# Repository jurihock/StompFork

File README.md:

# StompFork

This project is about an active audio signal splitter that utilizes the TL074 opamp to drive multiple parallel stompboxes.

## Key features

- Split one line-level input into three outputs
- Direct output (unity from input buffer)
- Stompbox output 1 (level pot + output buffer)
- Stompbox output 2 (level pot + output buffer)

## Power supply

- Recommended 18 V
- Should work at 12 V
- May work at 9 V
- Series schottky protection included

## Impedance

- Hi‑Z input (~1 MΩ AC)
- Lo‑Z output (~100 Ω AC)

## Caps

Depending on your preference, you can use polarized electrolytic caps in the signal path, or you can replace them with "audiophile" film caps. For this purpose, the KiCad project includes larger footprints for `C1` and `C5-C7`. 

If you decide to use the polarized electrolytic caps, ensure that the anode `+` is facing the opamp and the cathode `-` is facing the jacks.

Either way be sure to pick a sufficient voltage rating, e.g. 50 V.

## PCB

The circuit should fit on a standard 100x50 mm perfboard. You can save even more space by combining several smaller JST connectors into one larger one.

## Similar projects

- [The Splitter Kit](https://musikding.de/The-Splitter-kit) by [Das Musikding](https://musikding.de)
- [Signal Splitter](https://guitar-electronics.eu/en_US/c/SIGNAL-SPLITTER/68) by [Guitar Electronics](https://guitar-electronics.eu)

## Further reading

- [Designing With Opamps](https://sound-au.com/dwopa.htm) by [Rod Elliott](https://sound-au.com)

## Example build

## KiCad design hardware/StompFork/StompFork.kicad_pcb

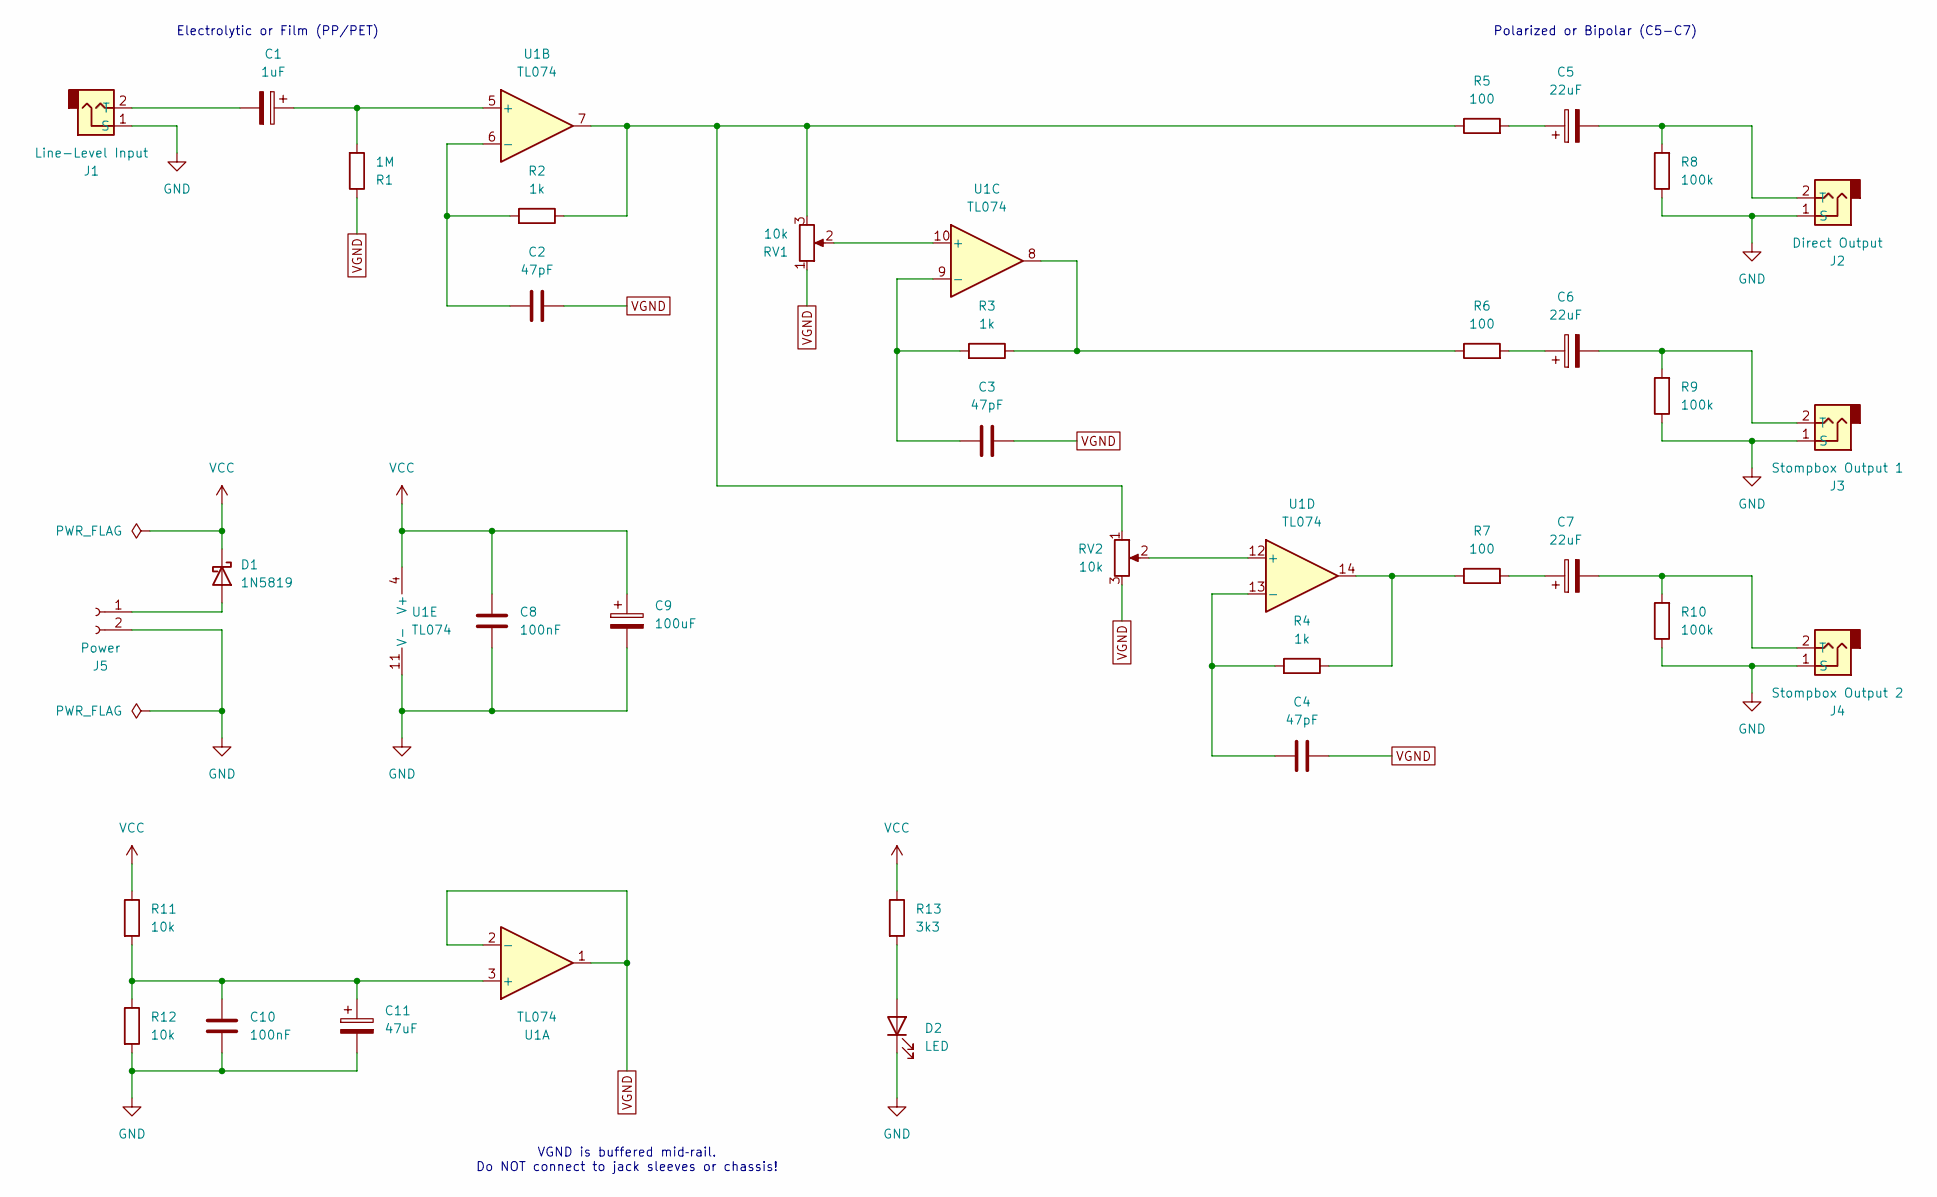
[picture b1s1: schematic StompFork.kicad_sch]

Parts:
C1: 1uF; CP_Axial_L18.0mm_D8.0mm_P25.00mm_Horizontal
C2, C3, C4: 47pF; C_Disc_D5.0mm_W2.5mm_P5.00mm
C5, C6, C7: 22uF; CP_Radial_D10.0mm_P5.00mm
C8, C10: 100nF; C_Disc_D5.0mm_W2.5mm_P5.00mm
C9: 100uF; CP_Radial_D6.3mm_P2.50mm
C11: 47uF; CP_Radial_D6.3mm_P2.50mm
D1: 1N5819; D_DO-41_SOD81_P10.16mm_Horizontal
D2: LED; JST_EH_B2B-EH-A_1x02_P2.50mm_Vertical
J1: Line-Level Input; JST_EH_B2B-EH-A_1x02_P2.50mm_Vertical
J2: Direct Output; JST_EH_B2B-EH-A_1x02_P2.50mm_Vertical
J3: Stompbox Output 1; JST_EH_B2B-EH-A_1x02_P2.50mm_Vertical
J4: Stompbox Output 2; JST_EH_B2B-EH-A_1x02_P2.50mm_Vertical
J5: Power; JST_EH_B2B-EH-A_1x02_P2.50mm_Vertical
R1: 1M; R_Axial_DIN0207_L6.3mm_D2.5mm_P2.54mm_Vertical
R2, R3, R4: 1k; R_Axial_DIN0207_L6.3mm_D2.5mm_P2.54mm_Vertical
R5, R6, R7: 100; R_Axial_DIN0207_L6.3mm_D2.5mm_P10.16mm_Horizontal
R8, R9, R10: 100k; R_Axial_DIN0207_L6.3mm_D2.5mm_P10.16mm_Horizontal
R11, R12: 10k; R_Axial_DIN0207_L6.3mm_D2.5mm_P10.16mm_Horizontal
R13: 3k3; R_Axial_DIN0207_L6.3mm_D2.5mm_P10.16mm_Horizontal
RV1, RV2: 10k; JST_EH_B3B-EH-A_1x03_P2.50mm_Vertical
U1: TL074; DIP-14_W7.62mm_Socket

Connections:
GND: C8.2, C9.2, C10.2, C11.2, D2.1 (K), J1.1 (S), J2.1 (S), J3.1 (S), J4.1 (S), J5.2, R8.1, R9.1, R10.1, R12.2, U1.11 (V-)
unnamed: C5.1, R5.2
unnamed: C6.1, R6.2
unnamed: C7.1, R7.2
unnamed: D1.2 (A), J5.1
unnamed: D2.2 (A), R13.2
unnamed: C1.2, J1.2 (T)
unnamed: C5.2, J2.2 (T), R8.2
unnamed: C6.2, J3.2 (T), R9.2
unnamed: C7.2, J4.2 (T), R10.2
unnamed: R2.1, R5.1, RV1.3, RV2.1, U1.7
unnamed: R3.1, R6.1, U1.8
unnamed: R4.1, R7.1, U1.14
unnamed: C10.1, C11.1, R11.2, R12.1, U1.3 (+)
unnamed: C1.1, R1.2, U1.5 (+)
unnamed: C2.1, R2.2, U1.6 (-)
unnamed: RV1.2, U1.10 (+)
unnamed: C3.1, R3.2, U1.9 (-)
unnamed: RV2.2, U1.12 (+)
unnamed: C4.1, R4.2, U1.13 (-)
VCC: C8.1, C9.1, D1.1 (K), R11.1, R13.1, U1.4 (V+)
VGND: C2.2, C3.2, C4.2, R1.1, RV1.1, RV2.3, U1.1, U1.2 (-)

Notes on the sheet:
Electrolytic or Film (PP/PET)
VGND is buffered mid‑rail. Do NOT connect to jack sleeves or chassis!
Polarized or Bipolar (C5-C7)

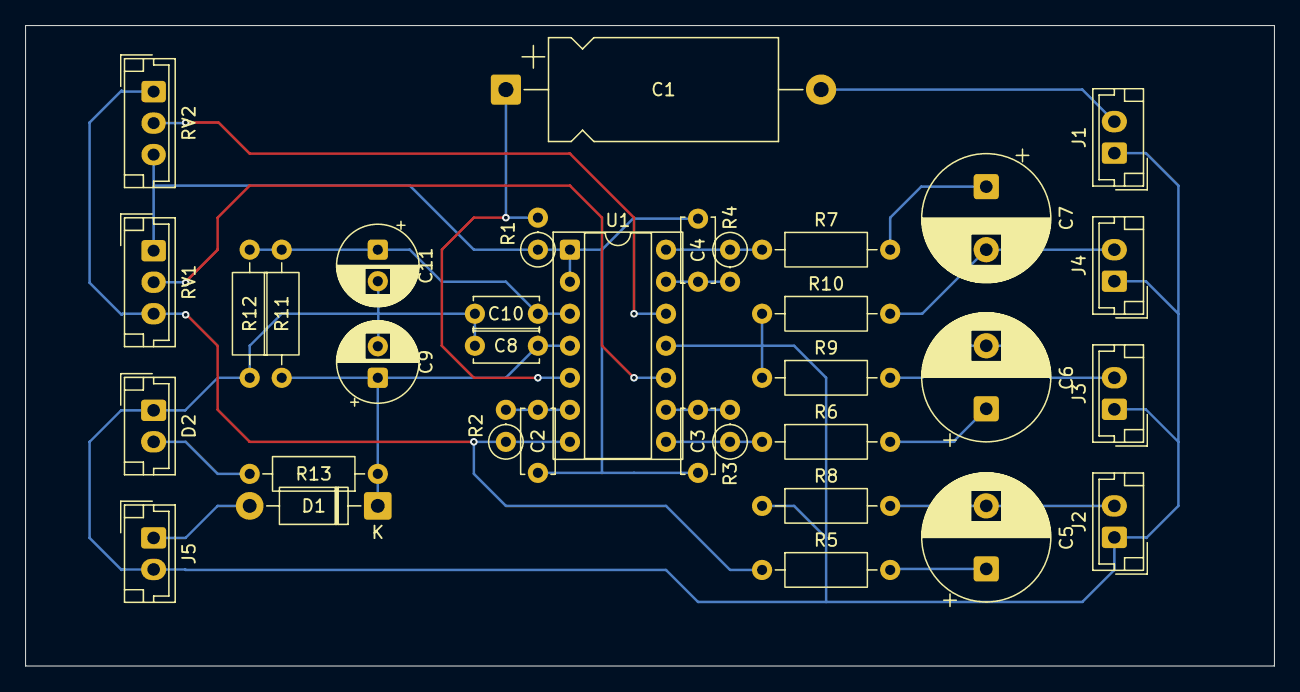
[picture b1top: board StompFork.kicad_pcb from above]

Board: 2 copper layers, 99.1 x 50.8 mm, 34 parts (0 on the bottom side), 22 nets.

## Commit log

2026-05-17 Create KiCad project
2026-05-17 Create sketch using unity buffers
2026-05-17 Add protection diode
2026-05-17 Fix feedback paths
2026-05-17 Polish schematic
2026-05-17 Update specs
2026-05-18 Fix typos
2026-05-18 Fix part number order
2026-05-18 Update power supply and impedance sections in README
2026-05-19 Update PCB
2026-05-20 Add status LED
2026-05-20 Rename VREF to VGND
2026-05-20 Fix VGND label placement
2026-05-20 Update comments
2026-05-20 Update labels
2026-05-21 Fix cap footprints
2026-06-07 Add images
